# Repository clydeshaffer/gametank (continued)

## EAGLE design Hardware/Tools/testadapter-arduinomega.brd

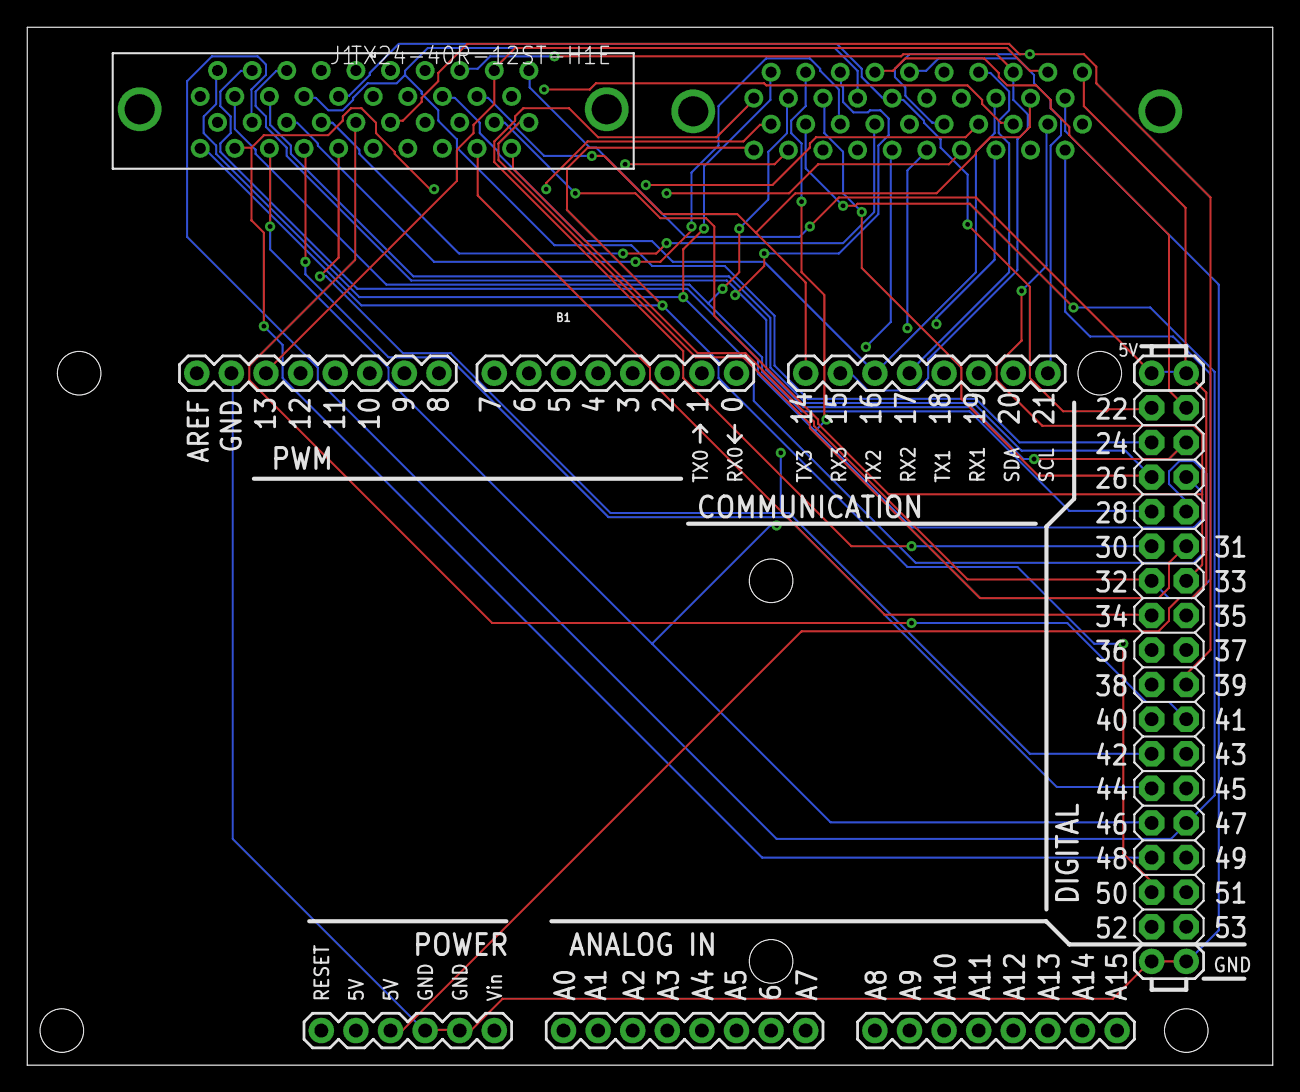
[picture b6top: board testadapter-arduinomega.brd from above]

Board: 4 copper layers, 91.4 x 76.2 mm, 3 parts (1 on the bottom side), 40 nets.

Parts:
B1: ARDUINO_MEGA_R3FULL; ARDUINO_MEGA
J1: TX24-40R-12ST-H1E; CON40_2X20_MU_TX24_JAE
J2: TX25-40P-6ST-H1E; CON40_2X20_MU_TX25_JAE

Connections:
GND: B1.GND@0, B1.GND@1, B1.GND@2, B1.GND@3, B1.GND@4, J1.2, J2.2
unnamed: B1.13, J1.3, J2.3
unnamed: B1.14, J1.4, J2.4
unnamed: B1.15, J1.5, J2.5
unnamed: B1.16, J1.6, J2.6
unnamed: B1.17, J1.7, J2.7
unnamed: B1.18, J1.8, J2.8
unnamed: B1.19, J1.9, J2.9
unnamed: B1.20, J1.10, J2.10
unnamed: B1.21, J1.11, J2.11
unnamed: B1.22, J1.12, J2.12
unnamed: B1.23, J1.13, J2.13
unnamed: B1.24, J1.14, J2.14
unnamed: B1.25, J1.15, J2.15
unnamed: B1.26, J1.16, J2.16
unnamed: B1.27, J1.17, J2.17
unnamed: B1.28, J1.18, J2.18
unnamed: B1.29, J1.19, J2.19
unnamed: B1.30, J1.20, J2.20
unnamed: B1.31, J1.21, J2.21
unnamed: B1.32, J1.22, J2.22
unnamed: B1.33, J1.23, J2.23
unnamed: B1.34, J1.24, J2.24
unnamed: B1.35, J1.25, J2.25
unnamed: B1.36, J1.26, J2.26
unnamed: B1.37, J1.27, J2.27
unnamed: B1.38, J1.28, J2.28
unnamed: B1.39, J1.29, J2.29
unnamed: B1.40, J1.30, J2.30
unnamed: B1.41, J1.31, J2.31
unnamed: B1.42, J1.32, J2.32
unnamed: B1.43, J1.33, J2.33
unnamed: B1.44, J1.34, J2.34
unnamed: B1.45, J1.35, J2.35
unnamed: B1.46, J1.36, J2.36
unnamed: B1.47, J1.37, J2.37
unnamed: B1.48, J1.38, J2.38
unnamed: B1.49, J1.39, J2.39
unnamed: B1.50, J1.40, J2.40
VCC: B1.5V@0, B1.5V@1, B1.5V@2, J1.1, J2.1

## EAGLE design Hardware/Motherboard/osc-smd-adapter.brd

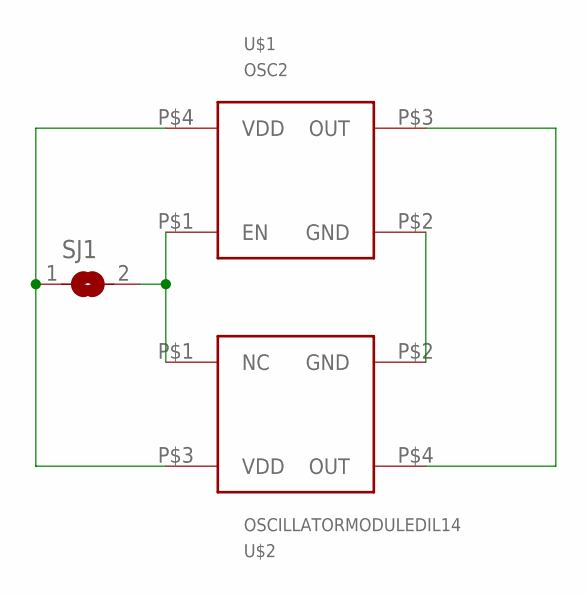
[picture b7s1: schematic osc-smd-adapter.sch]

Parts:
SJ1: SJ
U$1: OSC2; OSCPADS
U$2: OSCILLATORMODULEDIL14; CRYSTAL800MIL

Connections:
unnamed: SJ1.1, U$1.P$4 (VDD), U$2.P$3 (VDD)
unnamed: U$1.P$3 (OUT), U$2.P$4 (OUT)
unnamed: U$1.P$2 (GND), U$2.P$2 (GND)
unnamed: SJ1.2, U$1.P$1 (EN), U$2.P$1 (NC)

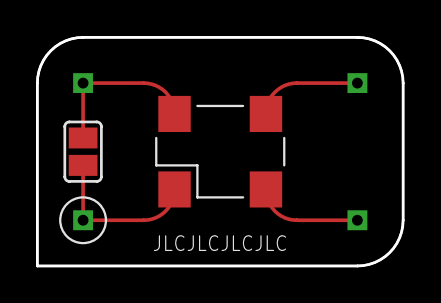
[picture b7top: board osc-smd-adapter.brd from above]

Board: 2 copper layers, 20.3 x 12.7 mm, 3 parts (0 on the bottom side), 4 nets.

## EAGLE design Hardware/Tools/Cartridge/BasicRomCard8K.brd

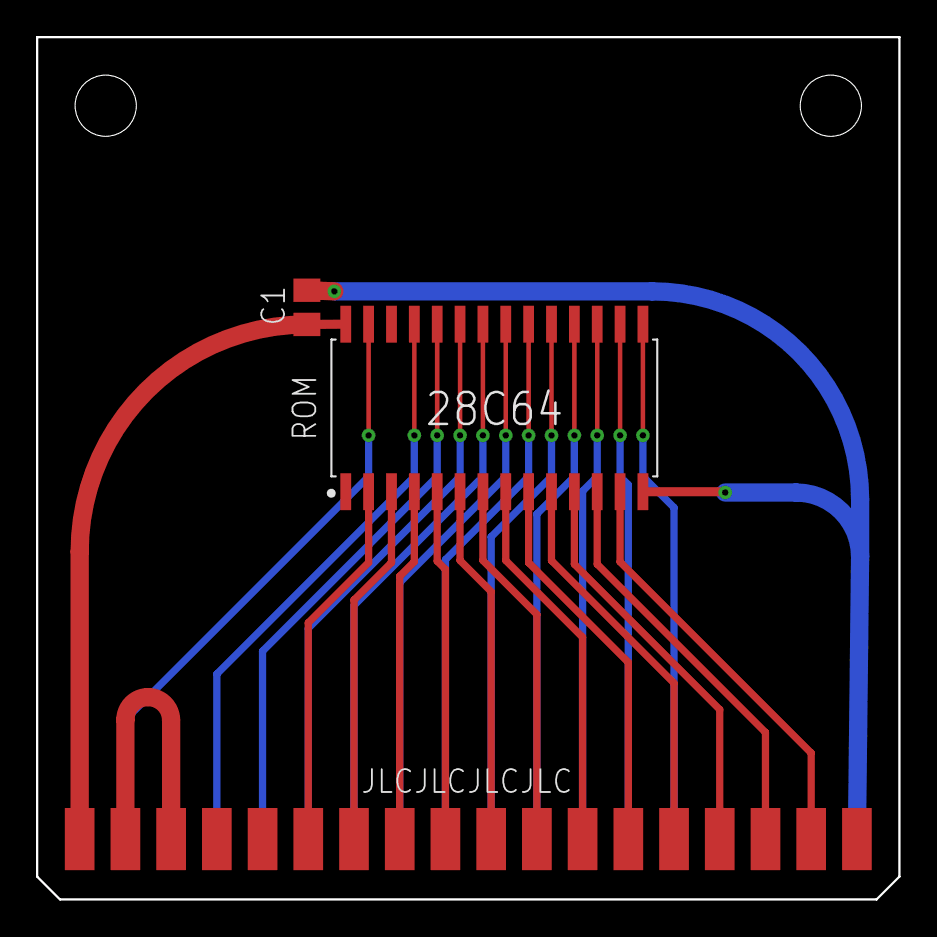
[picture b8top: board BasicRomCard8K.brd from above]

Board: 2 copper layers, 47.9 x 47.9 mm, 3 parts (0 on the bottom side), 27 nets.

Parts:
C1: C0805
ROM: 28C64SOIC28; SOIC127P1032X265-28
U$1: GT_CARTGT_CARD; CARD36

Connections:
!CS: ROM.20, U$1.P$28
!OE: ROM.22, U$1.P$30
!WE: ROM.27, U$1.P$35
A0: ROM.10, U$1.P$14
A1: ROM.9, U$1.P$13
A2: ROM.8, U$1.P$12
A3: ROM.7, U$1.P$11
A4: ROM.6, U$1.P$10
A5: ROM.5, U$1.P$9
A6: ROM.4, U$1.P$8
A7: ROM.3, U$1.P$7
A8: ROM.25, U$1.P$33
A9: ROM.24, U$1.P$32
A10: ROM.21, U$1.P$29
A11: ROM.23, U$1.P$31
A12: ROM.2, U$1.P$6
AUD_PASS: U$1.P$2, U$1.P$3
D0: ROM.11, U$1.P$15
D1: ROM.12, U$1.P$16
D2: ROM.13, U$1.P$17
D3: ROM.15, U$1.P$23
D4: ROM.16, U$1.P$24
D5: ROM.17, U$1.P$25
D6: ROM.18, U$1.P$26
D7: ROM.19, U$1.P$27
GND: C1.1, ROM.14, U$1.P$19
VCC: C1.2, ROM.28, U$1.P$1

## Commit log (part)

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2020-12-24 update blitter
2020-12-24 update libraries and add v2 soundcard
2021-04-24 regrettably I don't remember what I changed since the last commit
2021-05-01 Blitter V6 w/ 4-phase clock
2021-06-11 New Flash Cartridges
2021-06-11 Blitter fixes
2021-06-11 GameTank v3
2021-06-11 Move cartridge files into Tools
2021-06-11 Update production files
2021-06-23 Switched power module
2021-06-23 Add product lists for DigiKey and Mouser
2021-08-24 Updates to combined board inc. new blitter features
2022-06-05 RTC flash and power supply update
2022-07-22 Add case models
2022-07-22 Add experimental RTC cartridge
2022-07-22 Add cartridge shell models
2022-08-02 Add schematics in image form
2022-08-04 Upload PDF schematics
2022-08-27 Replacement PCB for THS7374 module
2022-08-30 add SMD oscillator to library and fix GRAM power connections
2022-08-31 fix ACP control lines (in schematic)
2022-09-03 Fix flipped SMD oscillator
2022-09-03 Replace MUX for readregs with spare gates
2022-09-29 Catridge adapter for Sanni reader and first draft of SRAM cartridge
2022-10-05 Add chip placement guides
2022-10-09 reorg STLs and add controller model
2022-11-03 more sram cart changes
2023-01-26 Reorganize Production (gerber zips) folder
2023-03-06 upload parts lists
2023-03-06 RAM cartridge fixes
2023-08-22 upload kicad conversions and smt versions
2023-08-22 some SRAM cartridge stuff
2023-08-22 convert Power module to KiCad
2023-08-23 power board kicad smt
2023-08-23 update kicad SMT BOMs
2023-11-28 SMT edits and start of fake dual ram sketching
2024-01-04 updates to kicad smt versions
2024-08-06 manual and models and misc hardware file updates
2024-08-20 Add new flasher v3
2024-08-20 update graphics on flasher v3
2024-08-20 fix unconnected nets in flasher3
2024-08-28 add footprint for reset controller on logic board and remove READY on cartridges
2024-08-29 megaprogrammer edit
2024-09-06 controller cad files and new cart flasher
2024-09-07 flasher2 sent for prototype production
2024-09-13 fix for smt controller
2025-07-05 add media files for presentations and websites etc
2025-10-03 collect production documents for quoting
2025-10-15 replace dual ported frame buffer with mirrored single ported rams
2025-10-15 design out the 4K dualport ram
2025-10-15 connect loose unused inputs to ground
2025-10-19 add svg of console badge
2025-10-19 add gamepad svg and iconified gametank image
2025-11-24 fix composite video generator board
2025-11-24 update manf brief
2025-12-01 Add quote files for molding
2025-12-01 Add AV board version with VRAM replaced but not ARAM
2025-12-01 update box label
2026-02-22 add draft of 2M cart with center hole
2026-03-05 mystery changes I forgot about on other computer and probably replicated and arent mergable oops
2026-03-05 warped checkerboard box
2026-03-05 more random updates
2026-03-06 mailer box cutout doc
2026-03-06 tweaks to gametank box template
2026-06-20 lots of emc tweaking, not done yet
2026-06-20 packaging update
2026-06-29 EMC updates part ?/?
